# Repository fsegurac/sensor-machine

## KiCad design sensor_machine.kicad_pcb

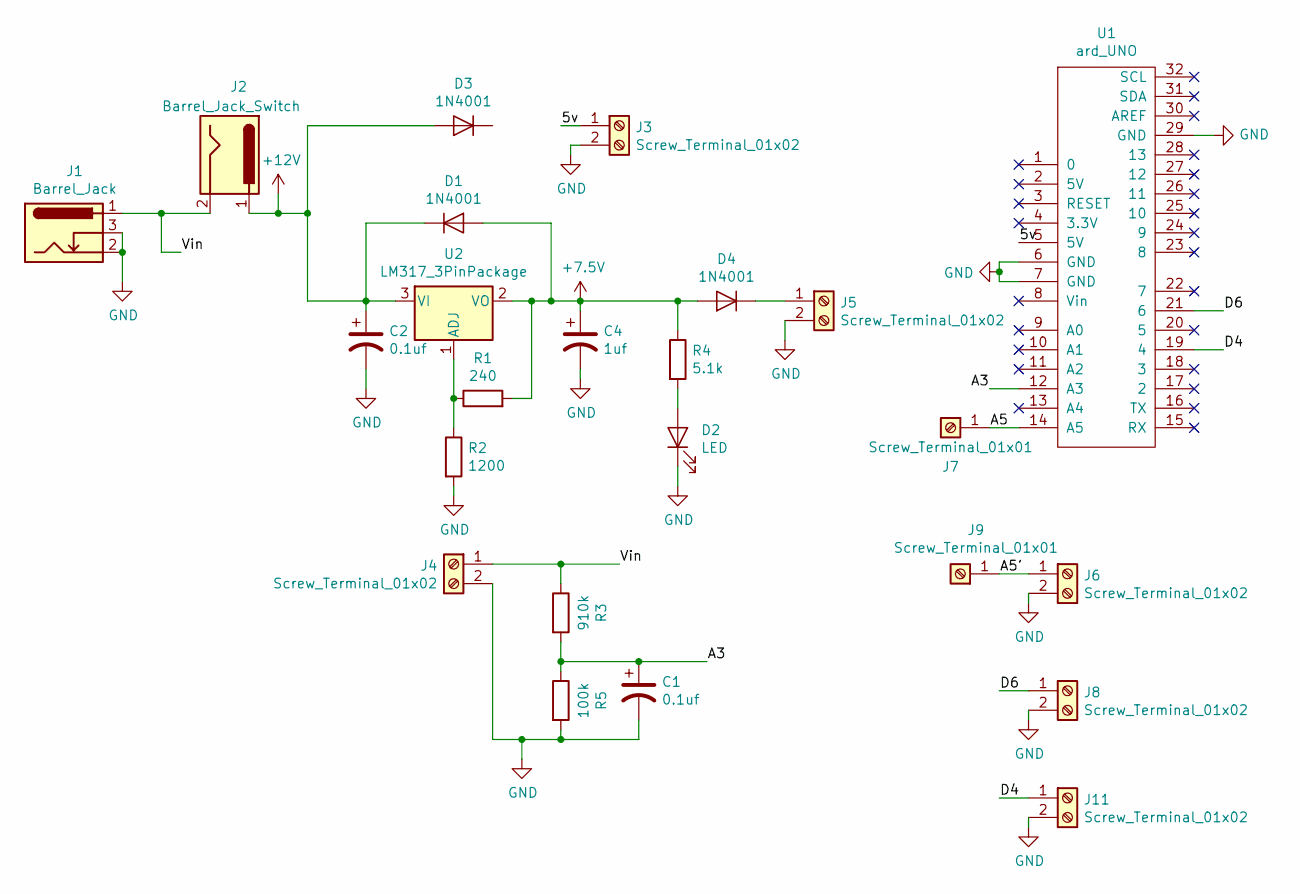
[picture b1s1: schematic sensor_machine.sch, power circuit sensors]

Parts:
C1, C2: 0.1uf; CP_Radial_D5.0mm_P2.00mm
C4: 1uf; C_0805_2012Metric_Pad1.15x1.40mm_HandSolder
D1, D3, D4: 1N4001; D_DO-41_SOD81_P10.16mm_Horizontal
D2: LED; LED_D4.0mm
J1: Barrel_Jack; BarrelJack_Horizontal
J2: Barrel_Jack_Switch; SW_DIP_SPSTx01_Slide_6.7x4.1mm_W7.62mm_P2.54mm_LowProfile
J3, J4, J5, J6, J8, J11: Screw_Terminal_01x02; TerminalBlock_Altech_AK300-2_P5.00mm
J7, J9: Screw_Terminal_01x01; Pin_d1.0mm_L10.0mm
R1: 240; R_Axial_DIN0207_L6.3mm_D2.5mm_P10.16mm_Horizontal
R2: 1200; R_Axial_DIN0207_L6.3mm_D2.5mm_P10.16mm_Horizontal
R3: 910k; R_Axial_DIN0207_L6.3mm_D2.5mm_P10.16mm_Horizontal
R4: 5.1k; R_Axial_DIN0207_L6.3mm_D2.5mm_P10.16mm_Horizontal
R5: 100k; R_Axial_DIN0207_L6.3mm_D2.5mm_P10.16mm_Horizontal
U1: ard_UNO; Arduino_UNO_R3_WithMountingHoles_handsoldering
U2: LM317_3PinPackage; TO-220-3_Vertical

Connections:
+7.5V: C4.1, D1.2 (A), D4.2 (A), R1.2, R4.1, U2.2 (VO)
+12V: C2.1, D1.1 (K), D3.2 (A), J2.1, U2.3 (VI)
/5v: J3.1, U1.5 (5V)
/A3: C1.1, R3.2, R5.1, U1.12 (A3)
/A5: J7.1, U1.14 (A5)
/A5': J6.1, J9.1
/D4: J11.1, U1.19 (4)
/D6: J8.1, U1.21 (6)
/Vin: J1.1, J2.2, J4.1, R3.1
GND: C1.2, C2.2, C4.2, D2.1 (K), J1.2, J1.3, J3.2, J4.2, J5.2, J6.2, J8.2, J11.2, R2.2, R5.2, U1.6 (GND), U1.7 (GND), U1.29 (GND)
unnamed: D2.2 (A), R4.2
unnamed: D4.1 (K), J5.1
unnamed: R1.1, R2.1, U2.1 (ADJ)

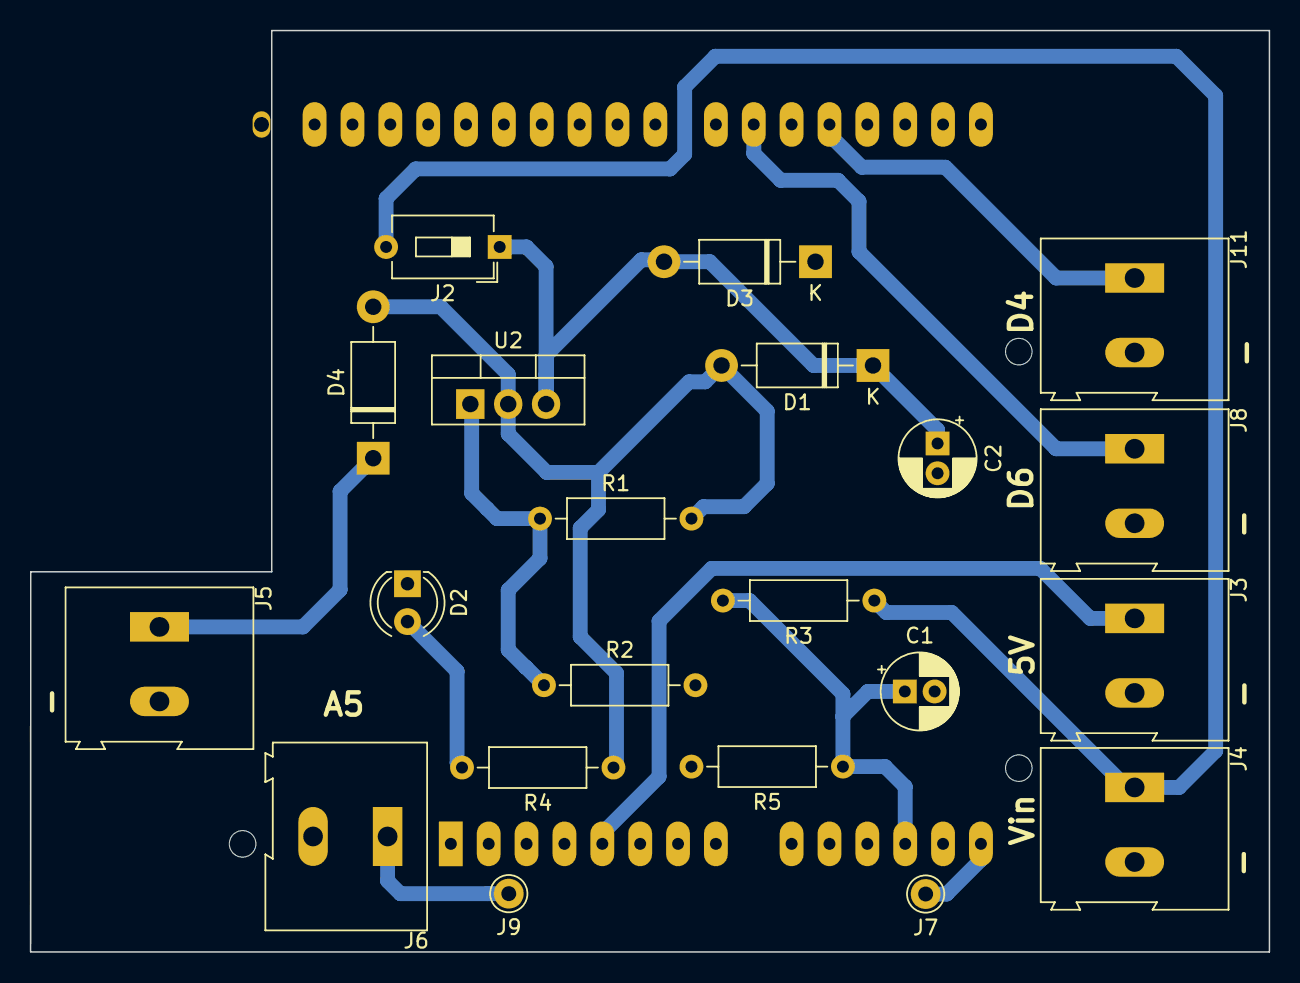
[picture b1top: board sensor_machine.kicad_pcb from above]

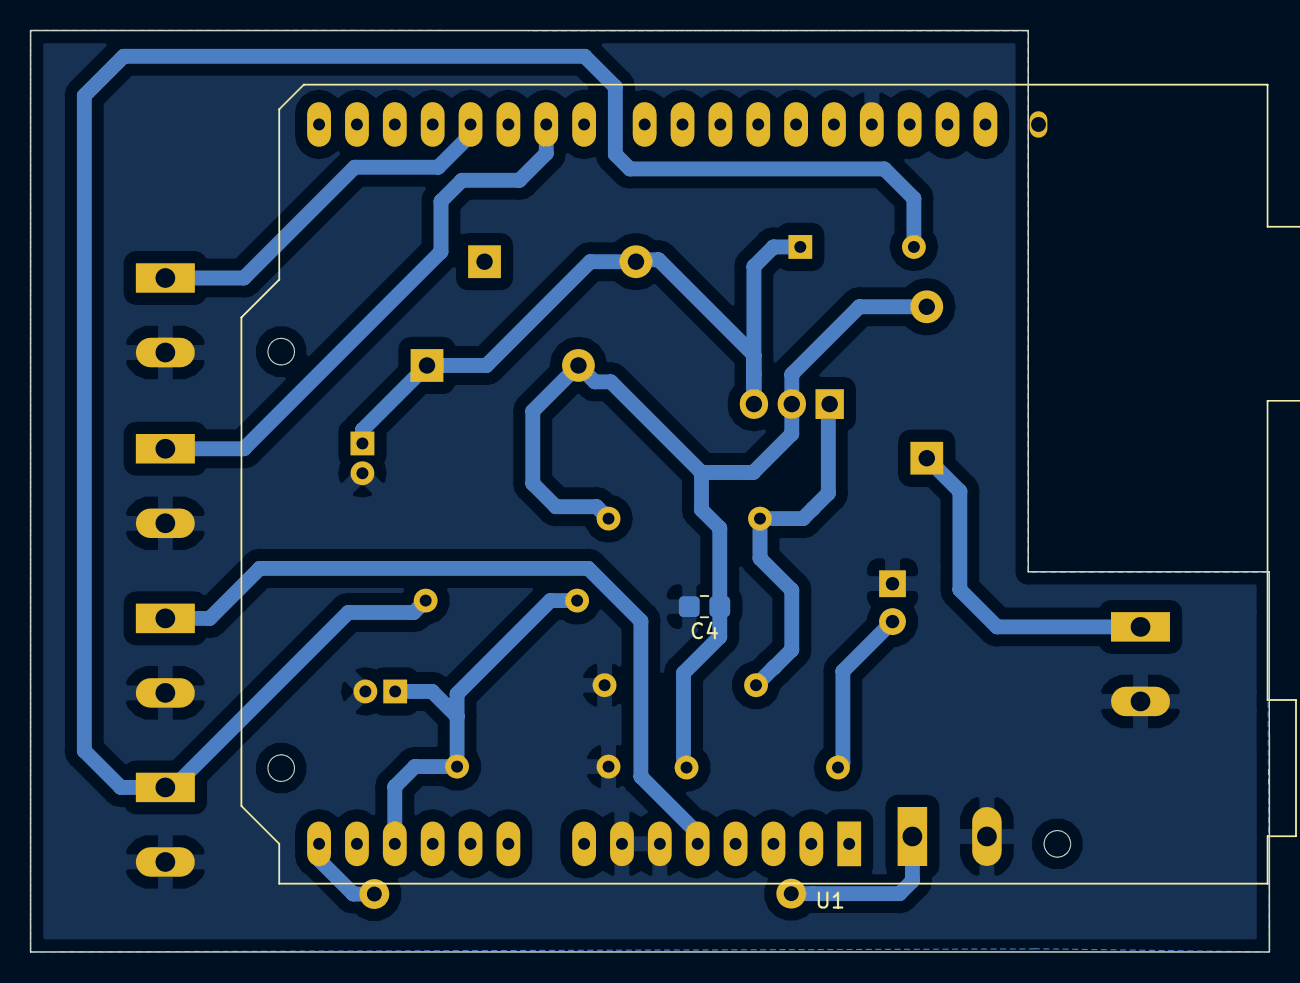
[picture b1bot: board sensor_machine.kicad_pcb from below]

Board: 2 copper layers, 83.1 x 61.8 mm, 23 parts (2 on the bottom side), 13 nets.

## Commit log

2019-08-09 power circuit sensors
2019-09-03 modificaciones pcb con arduino UNO
2019-09-09 reconfiguracion pcb
2019-09-15 correcciones pcb
2019-12-06 modificaciones PCB
